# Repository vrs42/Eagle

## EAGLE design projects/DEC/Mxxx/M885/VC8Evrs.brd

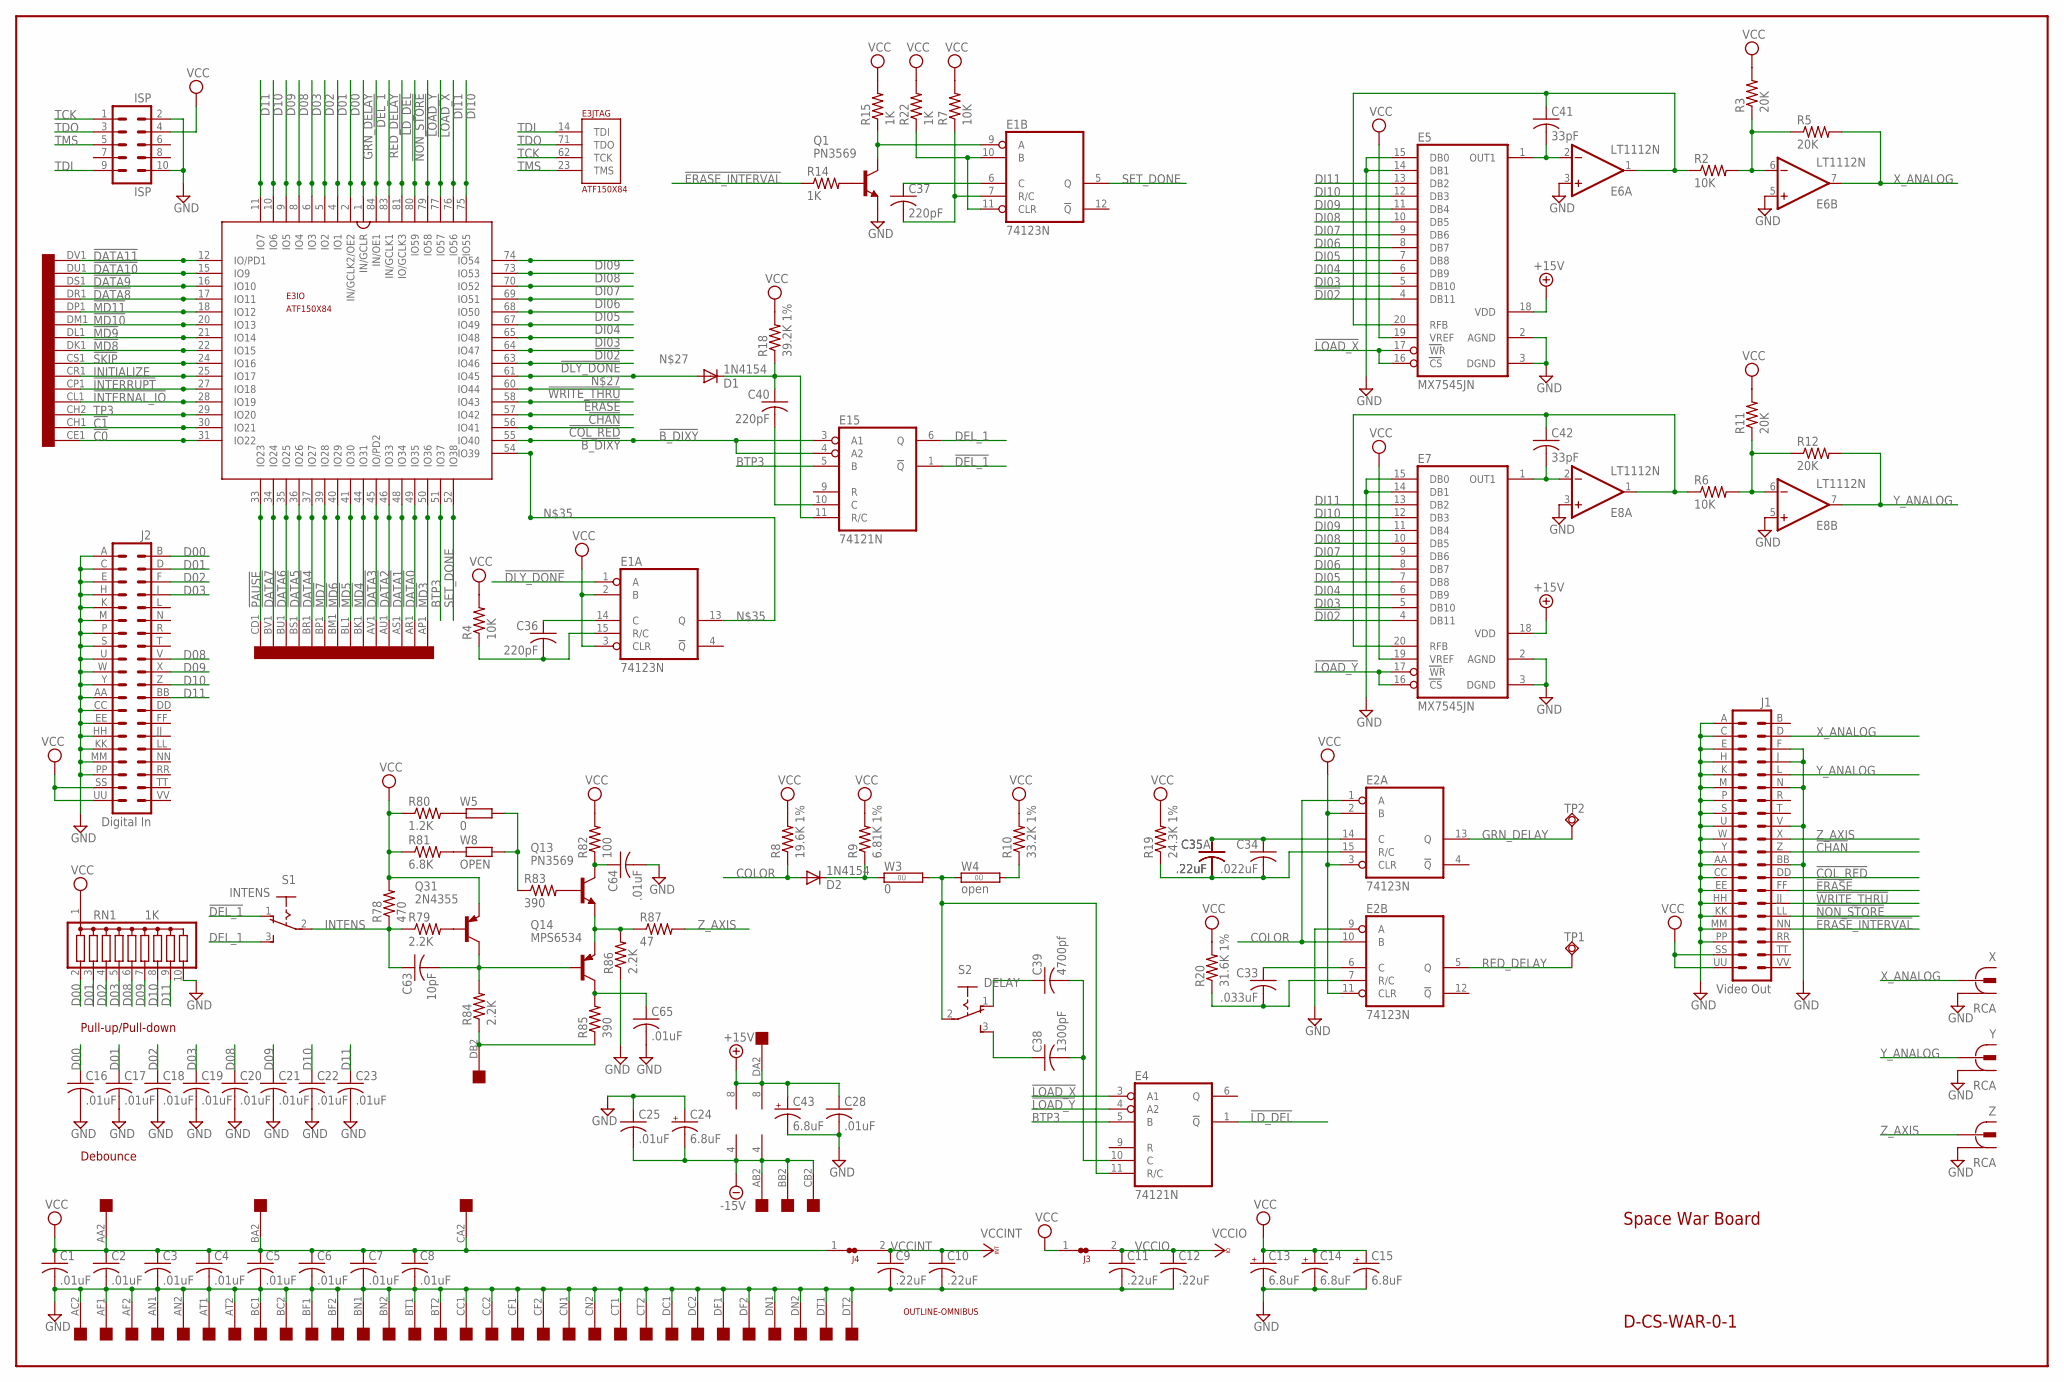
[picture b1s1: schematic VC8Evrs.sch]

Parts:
C1, C2, C3, C4, C5, C6, C7, C8, C16, C17, C18, C19, C20, C21, C22, C23, C25, C28, C64, C65: .01uF; C063-025X075
C9, C10, C11, C12: .22uF; C063-025X075
C13, C14, C15, C24, C43: 6.8uF; E12-8
C33: .033uF; C102-043X133
C34: .022uF; C102-043X133
C35: .22uF; C050-025X075
C35A: .22uF; C102-043X133
C36, C37, C40: 220pF; C063-025X075
C38: 1300pF; C150-054X183
C39: 4700pf; C102-043X133
C41, C42: 33pF; C063-025X075
C63: 10pF; C063-025X075
D1, D2: 1N4154; DO35-10
E1, E2: 74123N; DIL16
E3: ATF150X84; S84
E4, E15: 74121N; DIL14
E5, E7: MX7545JN; DIL20
E6, E8: LT1112N; DIL08
ISP: ISP; ML10
J1: Video Out; DEC40PINH
J2: Digital In; DEC40PINH
J3, J4: JUMPER-NC1; NC1
OMNIBUS: QUAD; EDGE-CON8
Q1: PN3569; TO18-
Q13: PN3569; TO5
Q14: MPS6534; TO5
Q31: 2N4355; TO5
R2, R4, R6, R7: 10K; 0207/10
R3, R5, R11, R12: 20K; 0207/10
R8: 19.6K 1%; 0207/15
R9: 6.81K 1%; 0207/15
R10: 33.2K 1%; 0207/15
R14, R15, R22: 1K; 0207/10
R18: 39.2K 1%; 0207/15
R19: 24.3K 1%; 0207/15
R20: 31.6K 1%; 0207/15
R78: 470; 0207/10
R79, R84, R86: 2.2K; 0207/10
R80: 1.2K; 0207/10
R81: 6.8K; 0207/10
R82: 100; 0207/10
R83, R85: 390; 0207/10
R87: 47; 0207/10
RN1: 1K; SIL10
S1: INTENS; M251
S2: DELAY; M251
TP1, TP2: TPSQPAD1-17; P1-17
U$1: OUTLINE-OMNIBUS; OMNIBUS
W3: 0; 0R/10
W4: open; 0R/10
W5: 0; 0207/10
W8: OPEN; 0207/10
X: RCA
Y: RCA
Z: RCA

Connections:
!B_DIXY: E3.55 (IO40), E15.3 (A1), E15.4 (A2)
!C0: E3.31 (IO22), OMNIBUS.CE1
!C1: E3.30 (IO21), OMNIBUS.CH1
!CHAN: E3.57 (IO42), J1.Z (22)
!COL_RED: E3.56 (IO41), J1.DD (26)
!DATA0: E3.49 (IO35), OMNIBUS.AR1
!DATA1: E3.48 (IO34), OMNIBUS.AS1
!DATA2: E3.46 (IO33), OMNIBUS.AU1
!DATA3: E3.45 (IO/PD2), OMNIBUS.AV1
!DATA4: E3.37 (IO27), OMNIBUS.BR1
!DATA5: E3.36 (IO26), OMNIBUS.BS1
!DATA6: E3.35 (IO25), OMNIBUS.BU1
!DATA7: E3.34 (IO24), OMNIBUS.BV1
!DATA8: E3.17 (IO11), OMNIBUS.DR1
!DATA9: E3.16 (IO10), OMNIBUS.DS1
!DATA10: E3.15 (IO9), OMNIBUS.DU1
!DATA11: E3.12 (IO/PD1), OMNIBUS.DV1
!DEL_1: E3.84 (IN/OE1), E15.1 (!Q), S1.1 (O)
!DI02: E3.64 (IO47), E5.4 (DB11), E7.4 (DB11)
!DLY_DONE: E1.1 (A), E3.63 (IO46)
!ERASE: E3.58 (IO43), J1.FF (28)
!ERASE_INTERVAL: J1.NN (34), R14.1
!INTERNAL_IO: E3.28 (IO19), OMNIBUS.CL1
!INTERRUPT: E3.27 (IO18), OMNIBUS.CP1
!LD_DEL: E3.81 (IO/GCLK3), E4.1 (!Q)
!LOAD_X: E3.77 (IO57), E4.3 (A1), E5.16 (CS), E5.17 (WR)
!LOAD_Y: E3.79 (IO58), E4.4 (A2), E7.16 (CS), E7.17 (WR)
!MD3: E3.50 (IO36), OMNIBUS.AP1
!MD4: E3.44 (IO31), OMNIBUS.BK1
!MD5: E3.41 (IO30), OMNIBUS.BL1
!MD6: E3.40 (IO29), OMNIBUS.BM1
!MD7: E3.39 (IO28), OMNIBUS.BP1
!MD8: E3.22 (IO15), OMNIBUS.DK1
!MD9: E3.21 (IO14), OMNIBUS.DL1
!MD10: E3.20 (IO13), OMNIBUS.DM1
!MD11: E3.18 (IO12), OMNIBUS.DP1
!NON_STORE: E3.80 (IO59), J1.LL (32)
!PAUSE: E3.33 (IO23), OMNIBUS.CD1
!SKIP: E3.24 (IO16), OMNIBUS.CS1
!WRITE_THRU: E3.60 (IO44), J1.JJ (30)
+15V: C28.1, C43.+, E5.18 (VDD), E6.8 (V+), E7.18 (VDD), E8.8 (V+), OMNIBUS.DA2
-15V: C24.-, C25.2, E6.4 (V-), E8.4 (V-), OMNIBUS.AB2, OMNIBUS.BB2, OMNIBUS.CB2
BTP3: E3.51 (IO37), E4.5 (B), E15.5 (B)
COLOR: D2.A, E2.1 (A), E2.10 (B), R8.1
D00: C16.1, E3.2 (IN/GCLK2/OE2), J2.B (2), RN1.2
D01: C17.1, E3.4 (IO1), J2.D (4), RN1.3
D02: C18.1, E3.5 (IO2), J2.F (6), RN1.4
D03: C19.1, E3.6 (IO3), J2.J (8), RN1.5
D08: C20.1, E3.8 (IO4), J2.V (18), RN1.6
D09: C21.1, E3.9 (IO5), J2.X (20), RN1.7
D10: C22.1, E3.10 (IO6), J2.Z (22), RN1.8
D11: C23.1, E3.11 (IO7), J2.BB (24), RN1.9
DEL_1: E15.6 (Q), S1.3 (S)
DI03: E3.65 (IO48), E5.5 (DB10), E7.5 (DB10)
DI04: E3.67 (IO49), E5.6 (DB9), E7.6 (DB9)
DI05: E3.68 (IO50), E5.7 (DB8), E7.7 (DB8)
DI06: E3.69 (IO51), E5.8 (DB7), E7.8 (DB7)
DI07: E3.70 (IO52), E5.9 (DB6), E7.9 (DB6)
DI08: E3.73 (IO53), E5.10 (DB5), E7.10 (DB5)
DI09: E3.74 (IO54), E5.11 (DB4), E7.11 (DB4)
DI10: E3.75 (IO55), E5.12 (DB3), E7.12 (DB3)
DI11: E3.76 (IO56), E5.13 (DB2), E7.13 (DB2)
GND: C1.2, C2.2, C3.2, C4.2, C5.2, C6.2, C7.2, C8.2, C9.2, C10.2, C11.2, C12.2, C13.-, C14.-, C15.-, C16.2, C17.2, C18.2, C19.2, C20.2, C21.2, C22.2, C23.2, C24.+, C25.1, C28.2, C43.-, C64.2, C65.2, E1.8 (GND), E2.8 (GND), E2.9 (A), E3.7 (GND), E3.19 (GND), E3.32 (GND), E3.42 (GND), E3.47 (GND), E3.59 (GND), E3.72 (GND), E3.82 (GND), E4.7 (GND), E5.2 (AGND), E5.3 (DGND), E5.14 (DB1), E5.15 (DB0), E6.3 (+IN), E6.5 (+IN), E7.2 (AGND), E7.3 (DGND), E7.14 (DB1), E7.15 (DB0), E8.3 (+IN), E8.5 (+IN), E15.7 (GND), ISP.2, ISP.10, J1.A (1), J1.AA (23), J1.BB (24), J1.C (3), J1.CC (25), J1.E (5), J1.EE (27), J1.F (6), J1.H (7), J1.HH (29), J1.J (8), J1.K (9), J1.KK (31), J1.M (11), J1.MM (33), J1.N (12), J1.P (13), J1.PP (35), J1.S (15), J1.U (17), J1.V (18), J1.W (19), J1.Y (21), J2.A (1), J2.AA (23), J2.C (3), J2.CC (25), J2.E (5), J2.EE (27), J2.H (7), J2.HH (29), J2.K (9), J2.KK (31), J2.M (11), J2.MM (33), J2.P (13), J2.PP (35), J2.S (15), J2.U (17), J2.W (19), J2.Y (21), OMNIBUS.AC2, OMNIBUS.AF1, OMNIBUS.AF2, OMNIBUS.AN1, OMNIBUS.AN2, OMNIBUS.AT1, OMNIBUS.AT2, OMNIBUS.BC1, OMNIBUS.BC2, OMNIBUS.BF1, OMNIBUS.BF2, OMNIBUS.BN1, OMNIBUS.BN2, OMNIBUS.BT1, OMNIBUS.BT2, OMNIBUS.CC1, OMNIBUS.CC2, OMNIBUS.CF1, OMNIBUS.CF2, OMNIBUS.CN1, OMNIBUS.CN2, OMNIBUS.CT1, OMNIBUS.CT2, OMNIBUS.DC1, OMNIBUS.DC2, OMNIBUS.DF1, OMNIBUS.DF2, OMNIBUS.DN1, OMNIBUS.DN2, OMNIBUS.DT1, OMNIBUS.DT2, Q1.1 (E), R86.1, RN1.10, X.1, X.1@1 (1), X.1@2 (1), Y.1, Y.1@1 (1), Y.1@2 (1), Z.1, Z.1@1 (1), Z.1@2 (1)
GRN_DELAY: E2.13 (Q), E3.1 (IN/GCLR), TP2.TP
INITIALIZE: E3.25 (IO17), OMNIBUS.CR1
INTENS: C63.1, R78.1, R79.1, S1.2
unnamed: C41.2, E5.1 (OUT1), E6.2 (-IN)
unnamed: E6.6 (-IN), R2.2, R3.1, R5.1
unnamed: C41.1, E5.20 (RFB), E6.1 (OUT), R2.1
unnamed: C39.1, S2.1 (O)
unnamed: C42.2, E7.1 (OUT1), E8.2 (-IN)
unnamed: E8.6 (-IN), R6.2, R11.1, R12.1
unnamed: C42.1, E7.20 (RFB), E8.1 (OUT), R6.1
unnamed: D1.A, E3.61 (IO45)
unnamed: C40.1, D1.C, E15.11 (R/C), R18.1
unnamed: C40.2, E15.10 (C)
unnamed: C34.2, C35.2, C35A.2, E2.15 (R/C), R19.1
unnamed: C33.2, E2.7 (R/C), R20.1
unnamed: C33.1, E2.6 (C)
unnamed: C34.1, C35.1, C35A.1, E2.14 (C)
unnamed: E1.13 (Q), E3.54 (IO39)
unnamed: C36.2, E1.15 (R/C), R4.1
unnamed: C36.1, E1.14 (C)
unnamed: Q1.2 (B), R14.2
unnamed: E1.9 (A), Q1.3 (C), R15.1
unnamed: E1.10 (B), E1.11 (CLR), R22.1
unnamed: C37.2, E1.7 (R/C), R7.1
unnamed: C37.1, E1.6 (C)
unnamed: D2.C, R9.1, W3.1
unnamed: E4.11 (R/C), S2.2, W3.2, W4.1
unnamed: R10.1, W4.2
unnamed: C38.1, S2.3 (S)
unnamed: C38.2, C39.2, E4.10 (C)
unnamed: Q31.2 (B), R79.2
unnamed: C63.2, Q14.2 (B), Q31.3 (C), R84.2
unnamed: OMNIBUS.DB2, R84.1, R85.1
unnamed: C65.1, Q14.3 (C), R85.2
unnamed: Q13.1 (E), Q14.1 (E), R86.2, R87.1
unnamed: R80.2, W5.1
unnamed: R81.2, W8.1
unnamed: Q13.2 (B), R83.2
unnamed: R83.1, W5.2, W8.2
unnamed: C64.1, Q13.3 (C), R82.1
RED_DELAY: E2.5 (Q), E3.83 (IN/GCLK1), TP1.TP
SET_DONE: E1.5 (Q), E3.52 (IO38)
TCK: E3.62 (TCK), ISP.1
TDI: E3.14 (TDI), ISP.9
TDO: E3.71 (TDO), ISP.3
TMS: E3.23 (TMS), ISP.5
TP3: E3.29 (IO20), OMNIBUS.CH2
VCC: C1.1, C2.1, C3.1, C4.1, C5.1, C6.1, C7.1, C8.1, C13.+, C14.+, C15.+, E1.2 (B), E1.3 (CLR), E1.16 (VCC), E2.2 (B), E2.3 (CLR), E2.11 (CLR), E2.16 (VCC), E4.14 (VCC), E5.19 (VREF), E7.19 (VREF), E15.14 (VCC), ISP.4, J1.SS (37), J1.UU (39), J2.SS (37), J2.UU (39), J3.1, J4.1, OMNIBUS.AA2, OMNIBUS.BA2, OMNIBUS.CA2, Q31.1 (E), R3.2, R4.2, R7.2, R8.2, R9.2, R10.2, R11.2, R15.2, R18.2, R19.2, R20.2, R22.2, R78.2, R80.1, R81.1, R82.2, RN1.1
VCCINT: C9.1, C10.1, E3.3 (VCCINT), E3.43 (VCCINT), J4.2
VCCIO: C11.1, C12.1, E3.13 (VCCIO), E3.26 (VCCIO), E3.38 (VCCIO), E3.53 (VCCIO), E3.66 (VCCIO), E3.78 (VCCIO), J3.2
X_ANALOG: E6.7 (OUT), J1.D (4), R5.2, X.2
Y_ANALOG: E8.7 (OUT), J1.L (10), R12.2, Y.2
Z_AXIS: J1.X (20), R87.2, Z.2

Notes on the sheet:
D-CS-WAR-0-1
Space War Board
Debounce
Pull-up/Pull-down

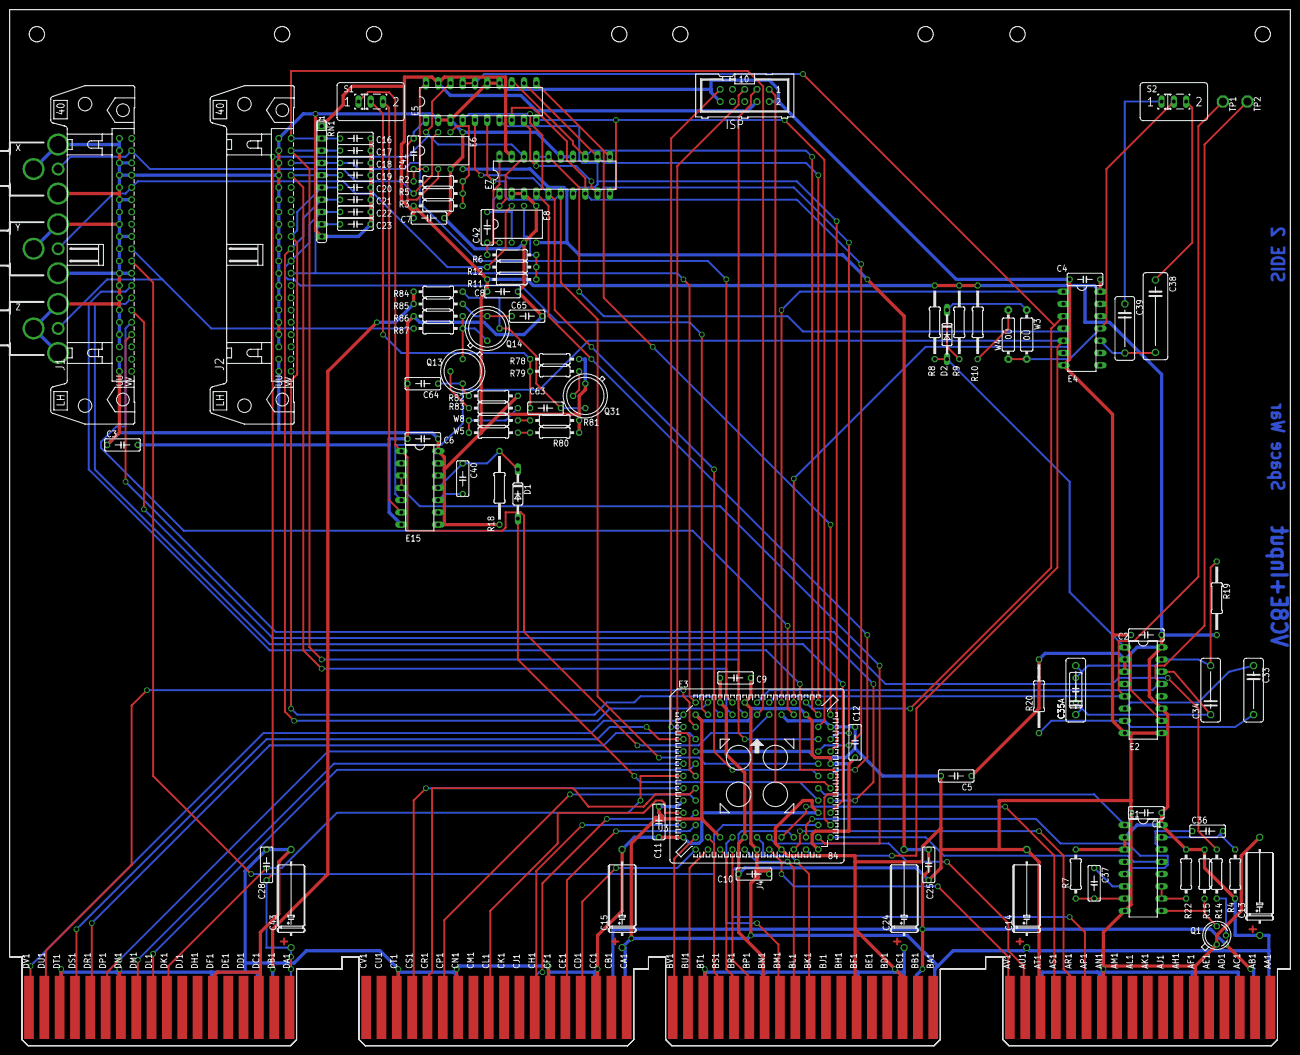
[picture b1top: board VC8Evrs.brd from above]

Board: 4 copper layers, 265.3 x 214.6 mm, 102 parts (0 on the bottom side), 116 nets.

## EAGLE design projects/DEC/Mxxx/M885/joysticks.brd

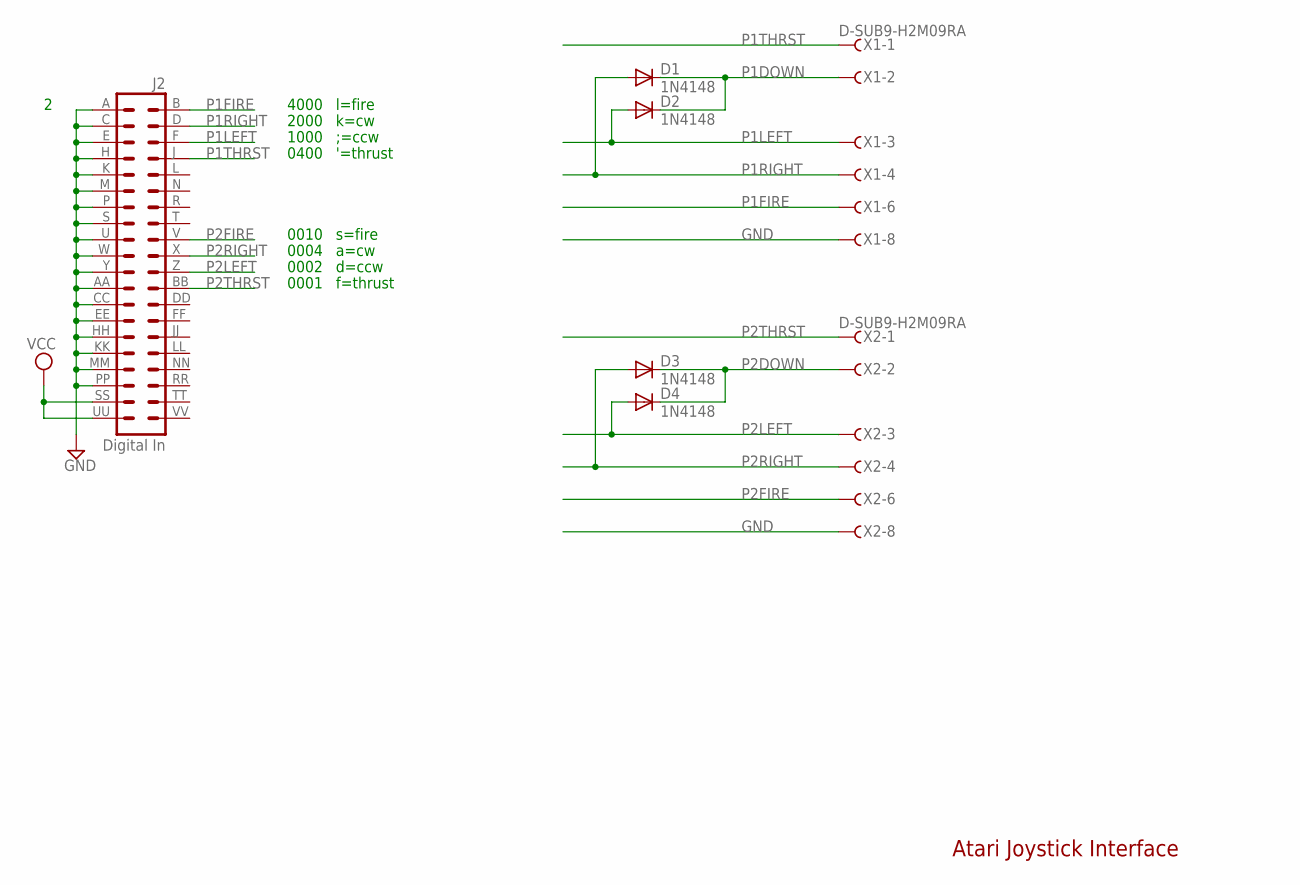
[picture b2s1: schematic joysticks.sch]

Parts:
D1, D2, D3, D4: 1N4148; DO35-10
J2: Digital In; DEC40PINH
X1, X2: D-SUB9-H2M09RA; H2M09RA

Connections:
GND: J2.A (1), J2.AA (23), J2.C (3), J2.CC (25), J2.E (5), J2.EE (27), J2.H (7), J2.HH (29), J2.K (9), J2.KK (31), J2.M (11), J2.MM (33), J2.P (13), J2.PP (35), J2.S (15), J2.U (17), J2.W (19), J2.Y (21), X1.8, X2.8
P1DOWN: D1.C, D2.C, X1.2
P1FIRE: J2.B (2), X1.6
P1LEFT: D2.A, J2.F (6), X1.3
P1RIGHT: D1.A, J2.D (4), X1.4
P1THRST: J2.J (8), X1.1
P2DOWN: D3.C, D4.C, X2.2
P2FIRE: J2.V (18), X2.6
P2LEFT: D4.A, J2.Z (22), X2.3
P2RIGHT: D3.A, J2.X (20), X2.4
P2THRST: J2.BB (24), X2.1
VCC: J2.SS (37), J2.UU (39)

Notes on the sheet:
Atari Joystick Interface
a=cw
s=fire
d=ccw
f=thrust
'=thrust
;=ccw
l=fire
k=cw
0001
0002
0004
0010
0400
4000
2000
1000

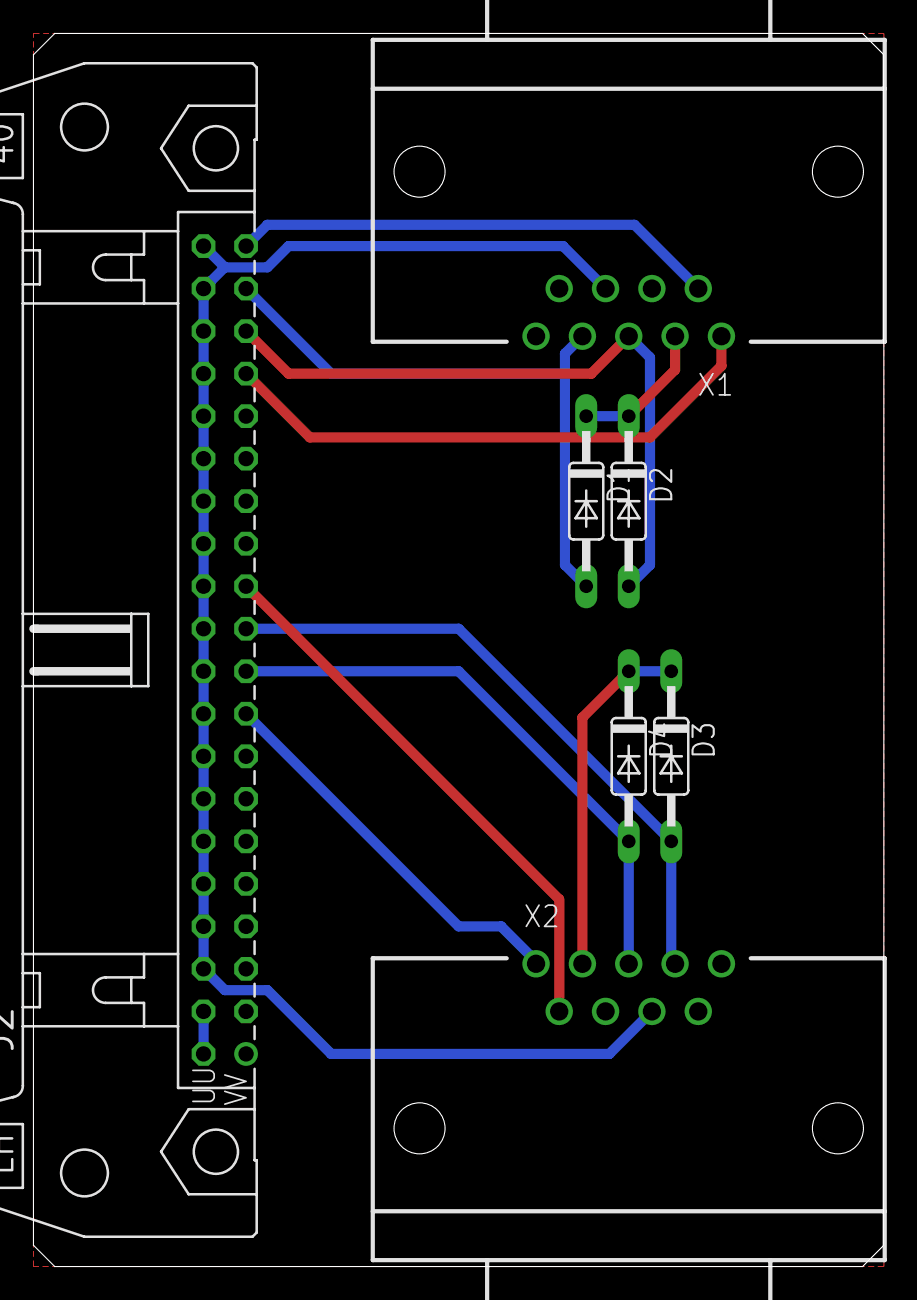
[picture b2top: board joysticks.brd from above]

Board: 2 copper layers, 50.8 x 73.7 mm, 7 parts (0 on the bottom side), 12 nets.

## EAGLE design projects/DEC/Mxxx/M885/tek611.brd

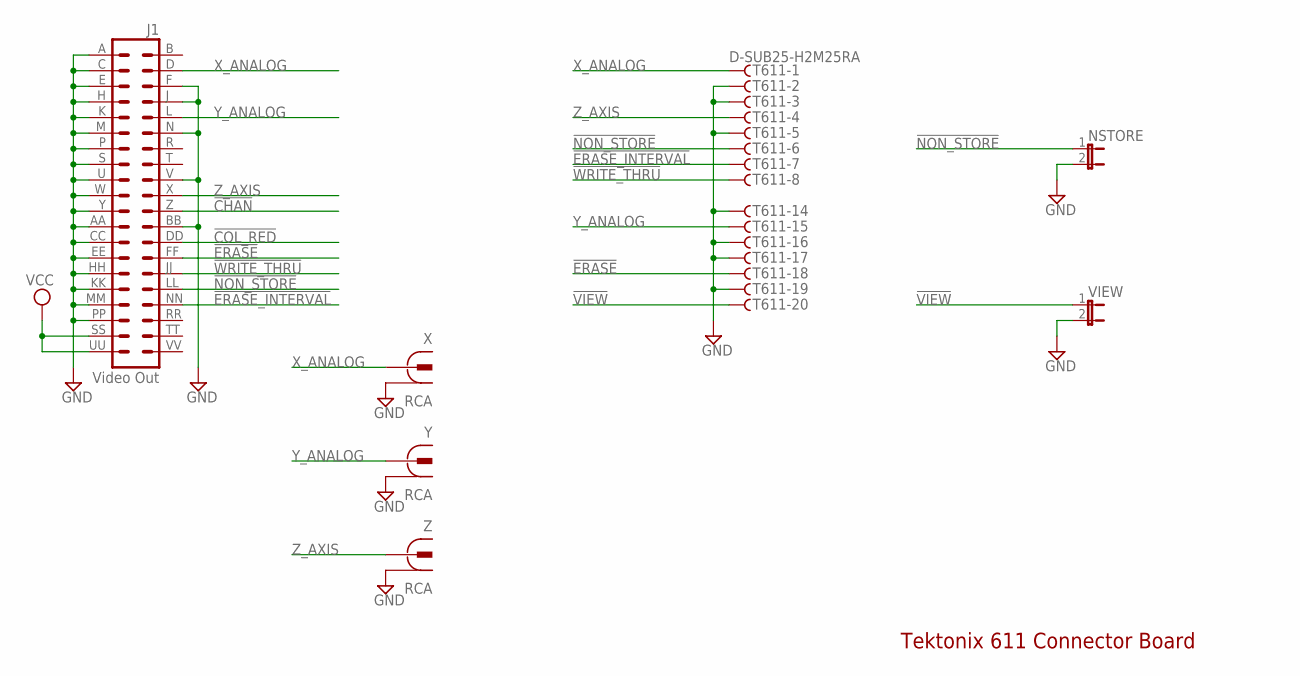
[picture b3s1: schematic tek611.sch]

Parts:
J1: Video Out; DEC40PINH
NSTORE: JP1
T611: D-SUB25-H2M25RA; H2M25RA
VIEW: JP1
X: RCA
Y: RCA
Z: RCA

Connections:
!CHAN: J1.Z (22)
!COL_RED: J1.DD (26)
!ERASE: J1.FF (28), T611.18
!ERASE_INTERVAL: J1.NN (34), T611.7
!NON_STORE: J1.LL (32), NSTORE.1, T611.6
!VIEW: T611.20, VIEW.1
!WRITE_THRU: J1.JJ (30), T611.8
GND: J1.A (1), J1.AA (23), J1.BB (24), J1.C (3), J1.CC (25), J1.E (5), J1.EE (27), J1.F (6), J1.H (7), J1.HH (29), J1.J (8), J1.K (9), J1.KK (31), J1.M (11), J1.MM (33), J1.N (12), J1.P (13), J1.PP (35), J1.S (15), J1.U (17), J1.V (18), J1.W (19), J1.Y (21), NSTORE.2, T611.2, T611.3, T611.5, T611.14, T611.16, T611.17, T611.19, VIEW.2, X.1, X.1@1 (1), X.1@2 (1), Y.1, Y.1@1 (1), Y.1@2 (1), Z.1, Z.1@1 (1), Z.1@2 (1)
VCC: J1.SS (37), J1.UU (39)
X_ANALOG: J1.D (4), T611.1, X.2
Y_ANALOG: J1.L (10), T611.15, Y.2
Z_AXIS: J1.X (20), T611.4, Z.2

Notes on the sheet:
Tektonix 611 Connector Board

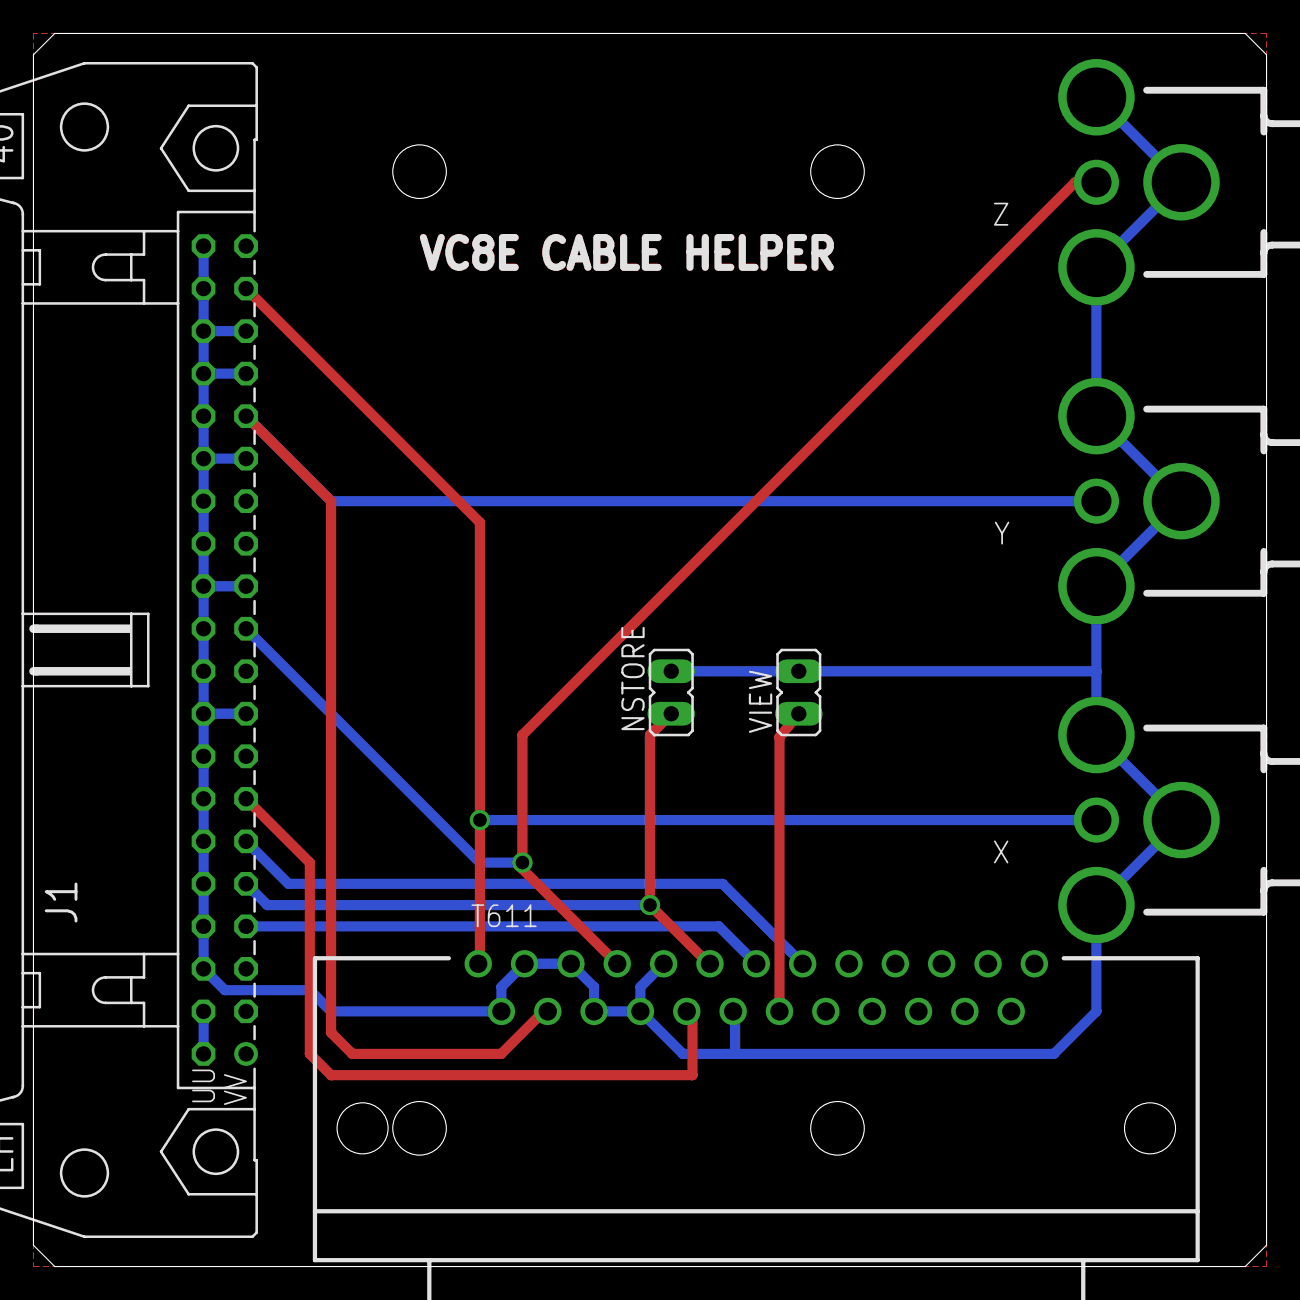
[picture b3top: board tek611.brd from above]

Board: 2 copper layers, 73.7 x 73.7 mm, 7 parts (0 on the bottom side), 10 nets.

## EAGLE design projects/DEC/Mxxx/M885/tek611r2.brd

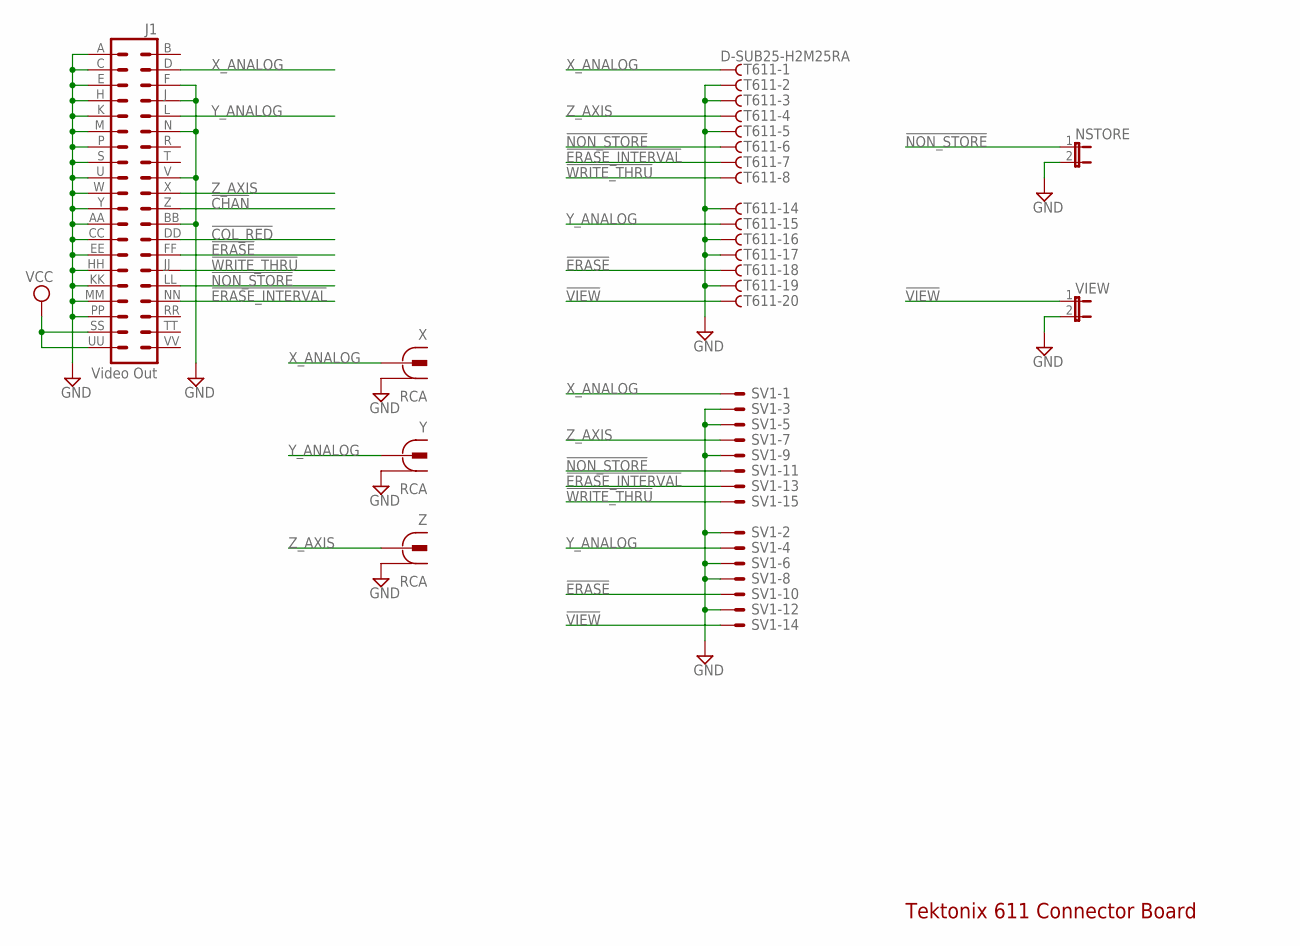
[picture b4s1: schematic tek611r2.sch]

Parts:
J1: Video Out; DEC40PINH
NSTORE: JP1
SV1: ML26L
T611: D-SUB25-H2M25RA; H2M25RA
VIEW: JP1
X: RCA
Y: RCA
Z: RCA

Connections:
!CHAN: J1.Z (22)
!COL_RED: J1.DD (26)
!ERASE: J1.FF (28), SV1.10, T611.18
!ERASE_INTERVAL: J1.NN (34), SV1.13, T611.7
!NON_STORE: J1.LL (32), NSTORE.1, SV1.11, T611.6
!VIEW: SV1.14, T611.20, VIEW.1
!WRITE_THRU: J1.JJ (30), SV1.15, T611.8
GND: J1.A (1), J1.AA (23), J1.BB (24), J1.C (3), J1.CC (25), J1.E (5), J1.EE (27), J1.F (6), J1.H (7), J1.HH (29), J1.J (8), J1.K (9), J1.KK (31), J1.M (11), J1.MM (33), J1.N (12), J1.P (13), J1.PP (35), J1.S (15), J1.U (17), J1.V (18), J1.W (19), J1.Y (21), NSTORE.2, SV1.2, SV1.3, SV1.5, SV1.6, SV1.8, SV1.9, SV1.12, T611.2, T611.3, T611.5, T611.14, T611.16, T611.17, T611.19, VIEW.2, X.1, X.1@1 (1), X.1@2 (1), Y.1, Y.1@1 (1), Y.1@2 (1), Z.1, Z.1@1 (1), Z.1@2 (1)
VCC: J1.SS (37), J1.UU (39)
X_ANALOG: J1.D (4), SV1.1, T611.1, X.2
Y_ANALOG: J1.L (10), SV1.4, T611.15, Y.2
Z_AXIS: J1.X (20), SV1.7, T611.4, Z.2

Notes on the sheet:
Tektonix 611 Connector Board

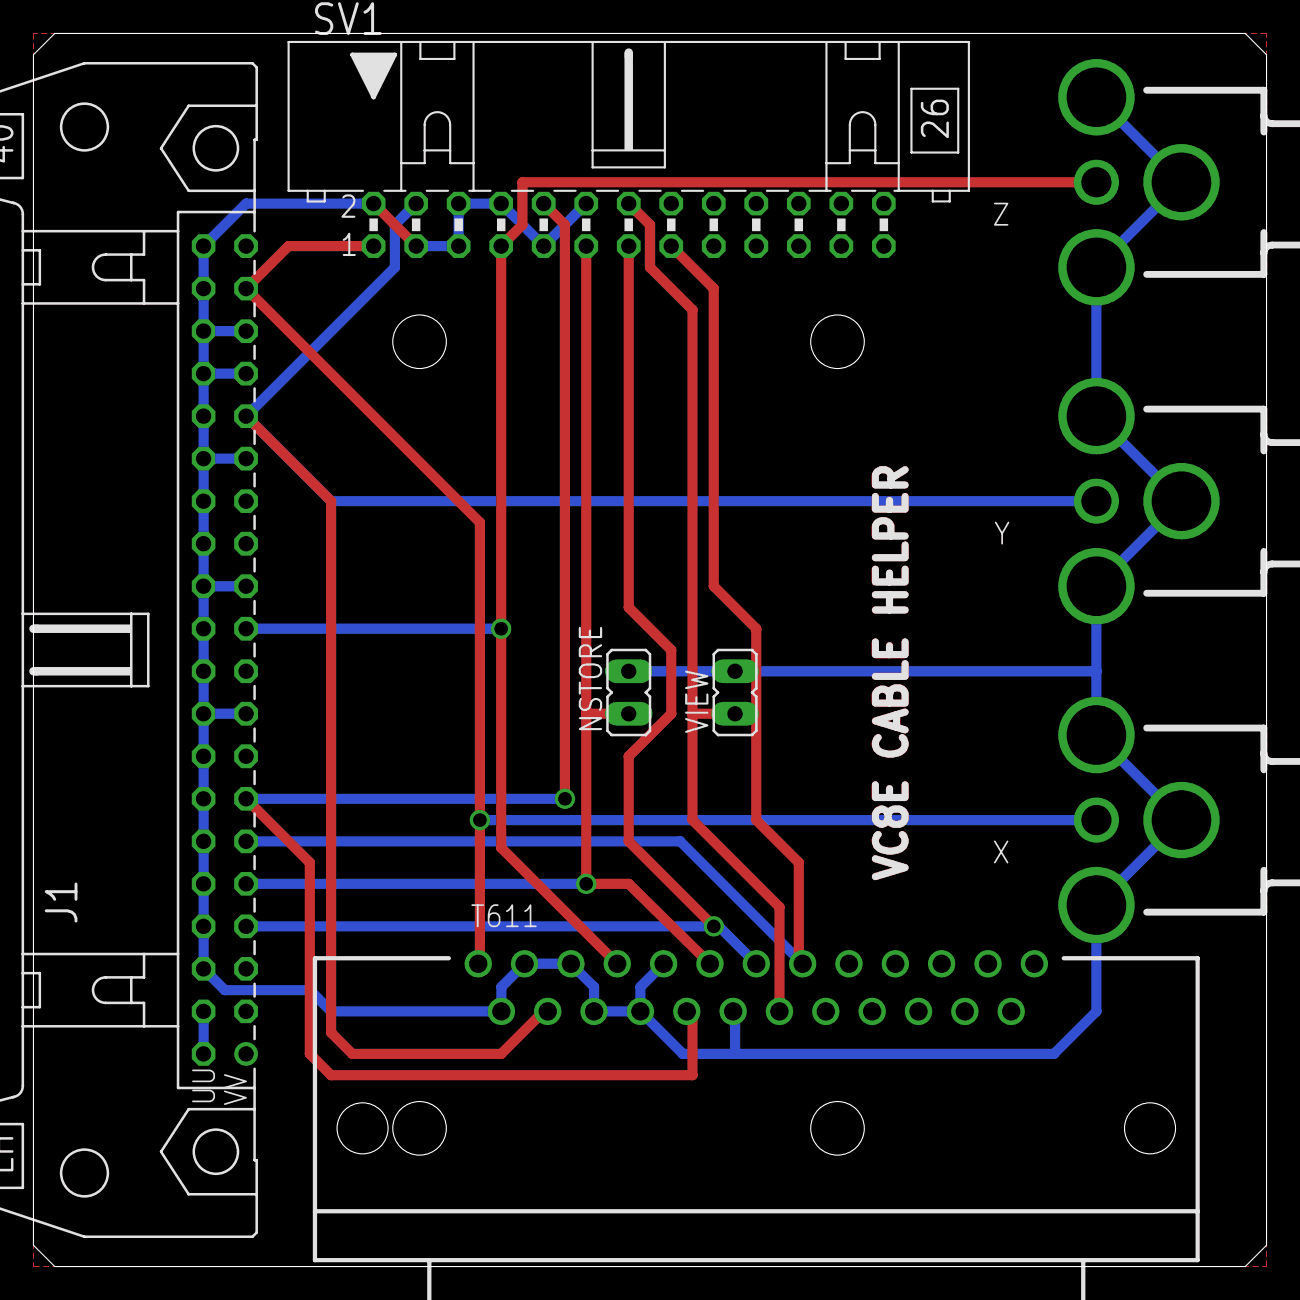
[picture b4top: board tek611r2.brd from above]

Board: 2 copper layers, 73.7 x 73.7 mm, 8 parts (0 on the bottom side), 10 nets.
